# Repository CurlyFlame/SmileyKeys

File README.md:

# SmileyKeys
SmileyKeys is a project for Highway Hackpad, which is a custom macropad that pushes expressiveness by being designed to do things other keyboards cannot do which is type in emojis. The hackpad features a set of 6 keys which are mapped to 6 emojis arranged in a smiley face pattern allowing the user to instantly react with those emojis. The hackpad also includes a rotary encoder to control and change the volume making SmileyKeys not only expressive but also pracical, ideal for those expressive tech users. 
# Schematic and PCB

# CAD

# Components
6x Cherry MX Switches

1x EC11 Rotary Encoder

2x SK6812 MINI LEDs

1x XIAO RP2040

Custom 3D Printed Top Case

Custom 3D Printed Bottom Case

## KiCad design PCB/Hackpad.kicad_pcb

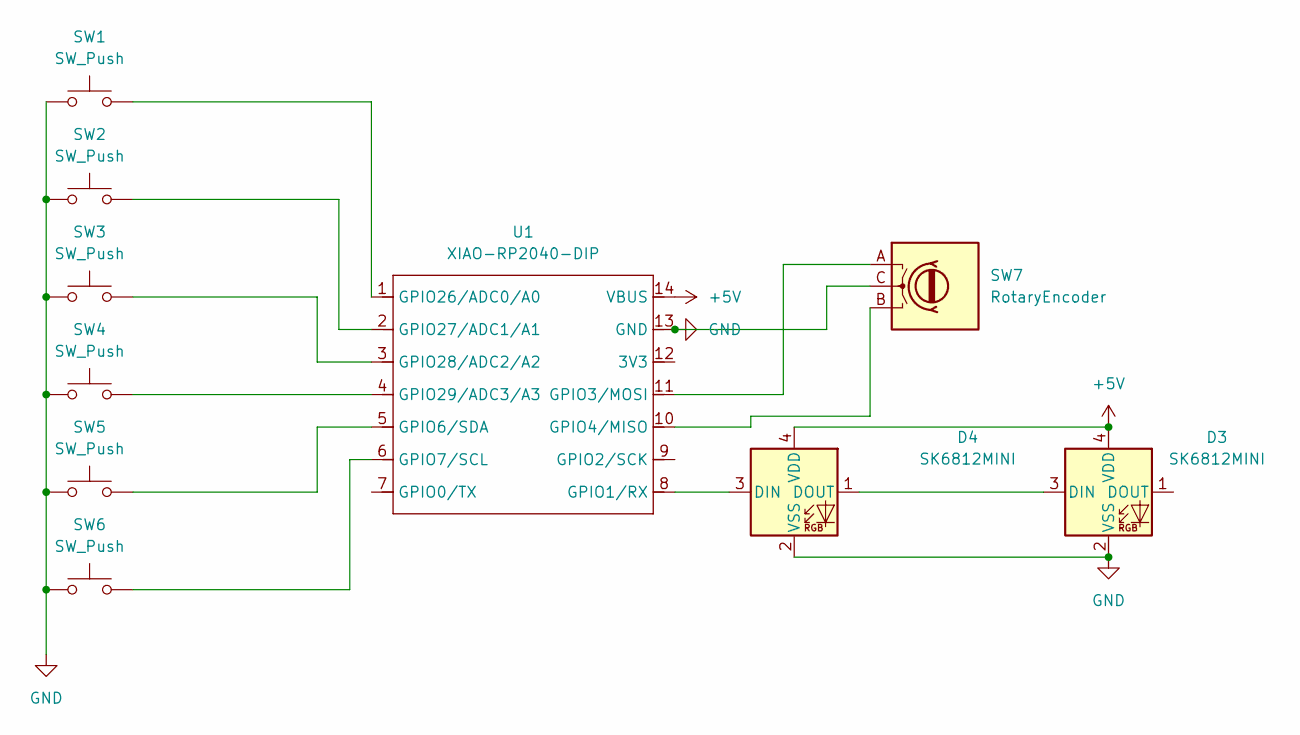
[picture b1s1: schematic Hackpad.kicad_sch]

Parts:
D3, D4: SK6812MINI; LED_SK6812MINI_PLCC4_3.5x3.5mm_P1.75mm
SW1, SW2, SW3, SW4, SW5, SW6: SW_Push; SW_Cherry_MX_1.00u_PCB
SW7: RotaryEncoder; RotaryEncoder_Alps_EC11E_Vertical_H20mm
U1: XIAO-RP2040-DIP

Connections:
+5V: D3.4 (VDD), D4.4 (VDD), U1.14 (VBUS)
GND: D3.2 (VSS), D4.2 (VSS), SW1.1, SW2.2, SW3.1, SW4.2, SW5.2, SW6.1, SW7.C, U1.13 (GND)
unnamed: D3.3 (DIN), D4.1 (DOUT)
unnamed: D4.3 (DIN), U1.8 (GPIO1/RX)
unnamed: SW7.A, U1.11 (GPIO3/MOSI)
unnamed: SW7.B, U1.10 (GPIO4/MISO)
unnamed: SW5.1, U1.5 (GPIO6/SDA)
unnamed: SW6.2, U1.6 (GPIO7/SCL)
unnamed: SW1.2, U1.1 (GPIO26/ADC0/A0)
unnamed: SW2.1, U1.2 (GPIO27/ADC1/A1)
unnamed: SW3.2, U1.3 (GPIO28/ADC2/A2)
unnamed: SW4.1, U1.4 (GPIO29/ADC3/A3)

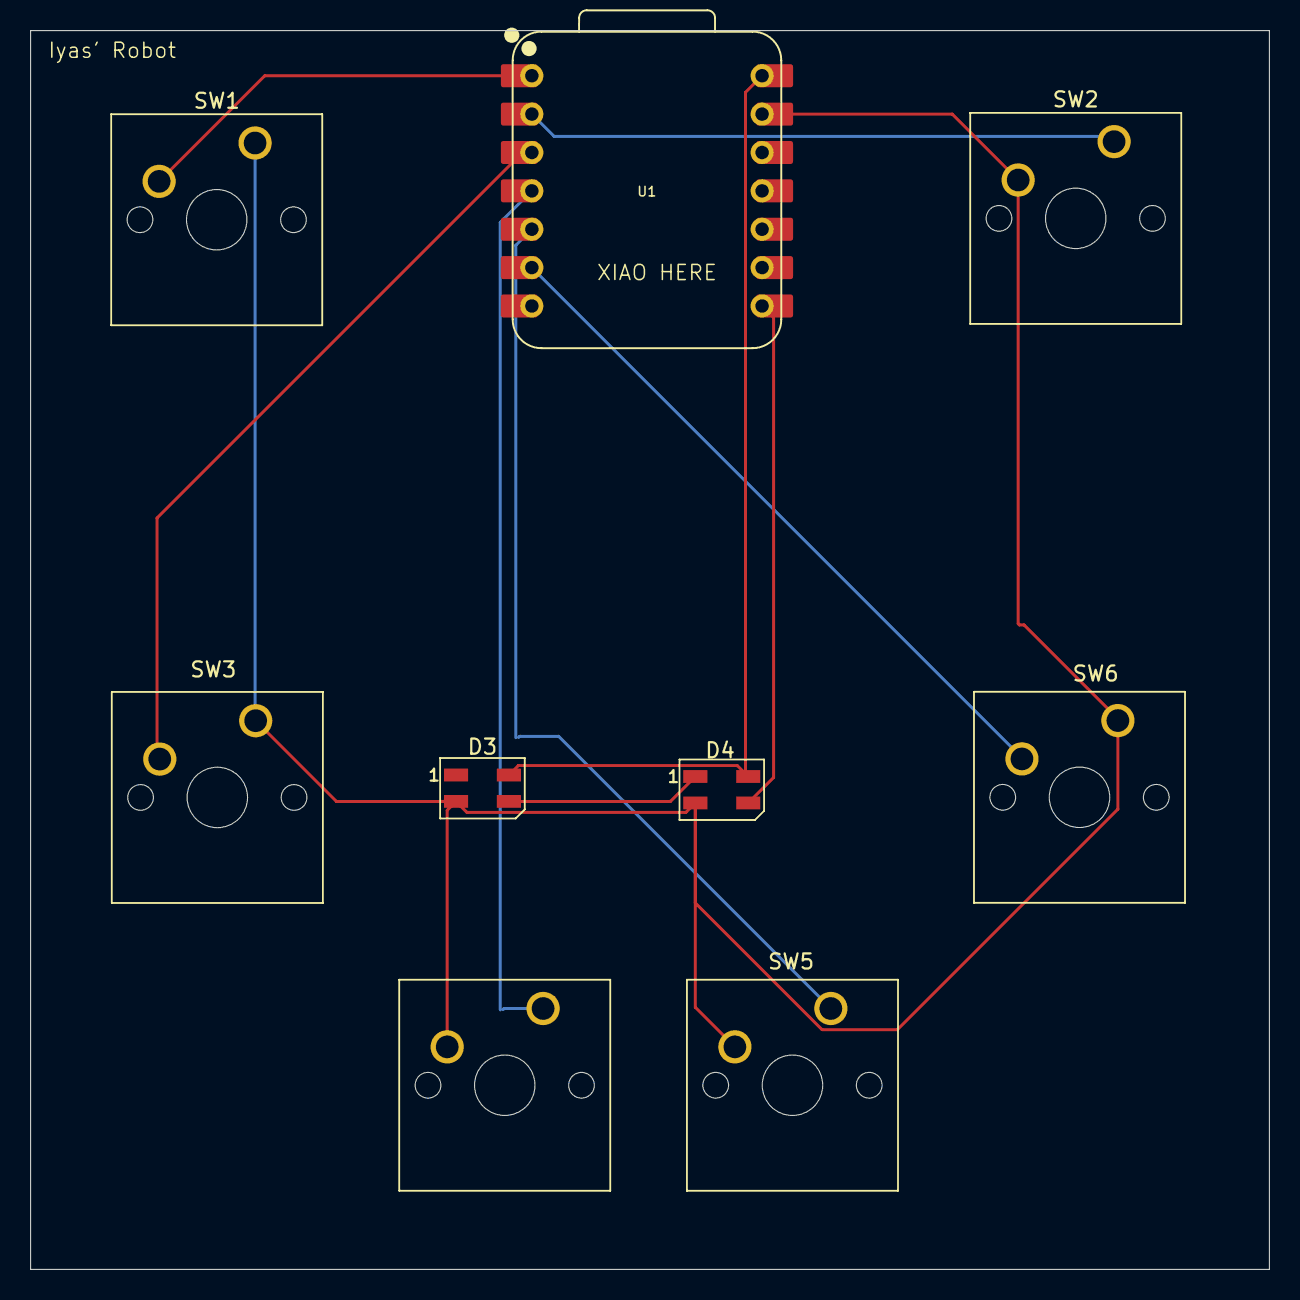
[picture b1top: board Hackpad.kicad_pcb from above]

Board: 2 copper layers, 82.0 x 82.0 mm, 9 parts (0 on the bottom side), 10 nets.
